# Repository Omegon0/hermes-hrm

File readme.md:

# amiHealthy
amiHealthy is not a device to measure if you're healthy. I just thought it was a fun name

What amiHealthy IS is a device that "measures" your heart rate and pulse oxygen levels (shoots light and reabsorbs it)
It's based off of the MAX30102 sensor that uses the difference between red and IR light to determine how oxygenated the blood is. By reading this a LOT of times per second, it can determine what your heart rate is by sensing how that level changes. And it detects SpO2 by detecting the difference in how much IR vs red is absorbed vs reflected by the blood. Really cool concept.

### Why does amiHealthy have a TOF sensor?

It uses the TOF sensor to know when the user is close to the device, so whether to enable the MAX30102 sensor. 

### Images

NOTE: I switched to kicad 9 for this project and it broke some of the rendering so the front and back of the board have some issues that I wasn't able to work out before hermes deadline

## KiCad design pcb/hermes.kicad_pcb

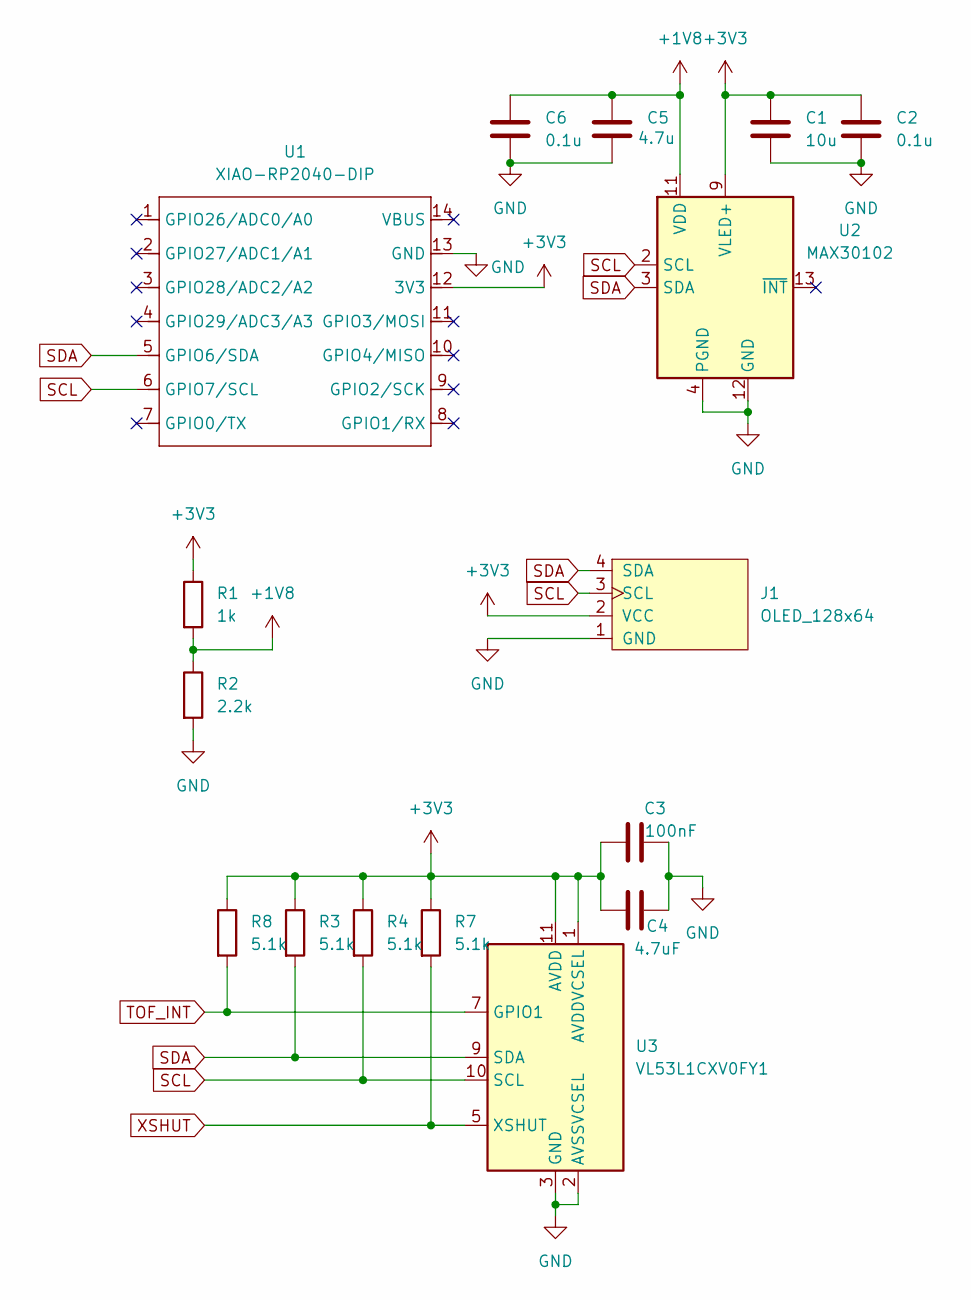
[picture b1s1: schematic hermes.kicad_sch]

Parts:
C1: 10u; C_0805_2012Metric
C2, C6: 0.1u; C_0805_2012Metric
C3: 100nF; C_0805_2012Metric
C4: 4.7uF; C_0805_2012Metric
C5: 4.7u; C_0805_2012Metric
J1: OLED_128x64; 128x64OLED
R1: 1k; R_0805_2012Metric
R2: 2.2k; R_0805_2012Metric
R3, R4, R7, R8: 5.1k; R_0805_2012Metric
U1: XIAO-RP2040-DIP
U2: MAX30102; Maxim_OLGA-14_3.3x5.6mm_P0.8mm
U3: VL53L1CXV0FY1; ST_VL53L1x

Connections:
+1V8: C5.1, C6.1, R1.2, R2.1, U2.11 (VDD)
+3V3: C1.1, C2.1, C3.1, C4.1, J1.2 (VCC), R1.1, R3.1, R4.1, R7.1, R8.1, U1.12 (3V3), U2.9 (VLED+), U2.10 (VLED+), U3.1 (AVDDVCSEL), U3.11 (AVDD)
GND: C1.2, C2.2, C3.2, C4.2, C5.2, C6.2, J1.1 (GND), R2.2, U1.13 (GND), U2.4 (PGND), U2.12 (GND), U3.2 (AVSSVCSEL), U3.3 (GND), U3.4 (GND), U3.6 (GND), U3.12 (GND)
SCL: J1.3 (SCL), R4.2, U1.6 (GPIO7/SCL), U2.2 (SCL), U3.10 (SCL)
SDA: J1.4 (SDA), R3.2, U1.5 (GPIO6/SDA), U2.3 (SDA), U3.9 (SDA)
TOF_INT: R8.2, U3.7 (GPIO1)
XSHUT: R7.2, U3.5 (XSHUT)

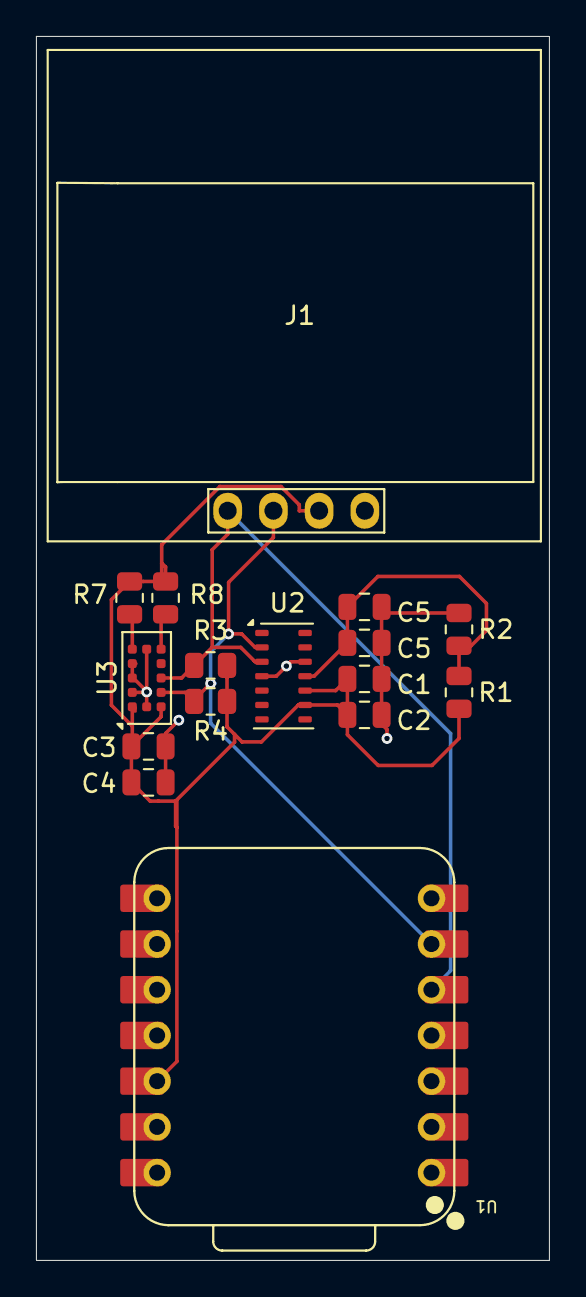
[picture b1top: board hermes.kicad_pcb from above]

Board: 2 copper layers, 28.5 x 68.0 mm, 16 parts (0 on the bottom side), 7 nets.

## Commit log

2025-08-03 added everything
2025-08-03 added iamges + readme
2025-08-21 reroute board to incorporate TOF sensor
2025-08-31 added readme
